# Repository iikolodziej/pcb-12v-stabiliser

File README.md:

# pcb-12v-stabiliser
pcb 12v stabiliser

# schematic

# pcb

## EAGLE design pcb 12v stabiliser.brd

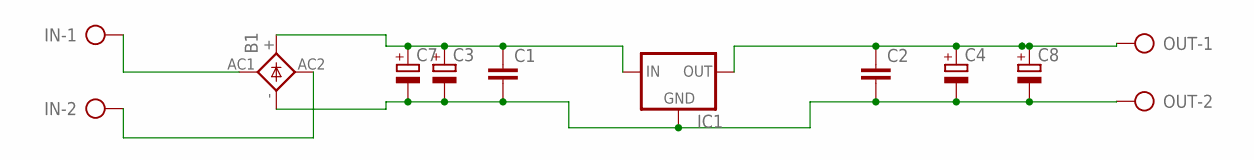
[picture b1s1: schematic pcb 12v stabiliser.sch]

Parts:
B1: 2KBB-R
C1, C2: C5/5; C5B5
C3, C4: CPOL-EUE5-8.5; E5-8,5
C7, C8: CPOL-EUE5-10.5; E5-10,5
IC1: 78XXS
IN: AK500/2-H
OUT: AK500/2-H

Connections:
GND: B1.-, C1.2, C2.2, C3.-, C4.-, C7.-, C8.-, IC1.GND, OUT.2
unnamed: B1.AC1, IN.1
unnamed: B1.AC2, IN.2
unnamed: B1.+, C1.1, C3.+, C7.+, IC1.IN
unnamed: C2.1, C4.+, C8.+, IC1.OUT, OUT.1

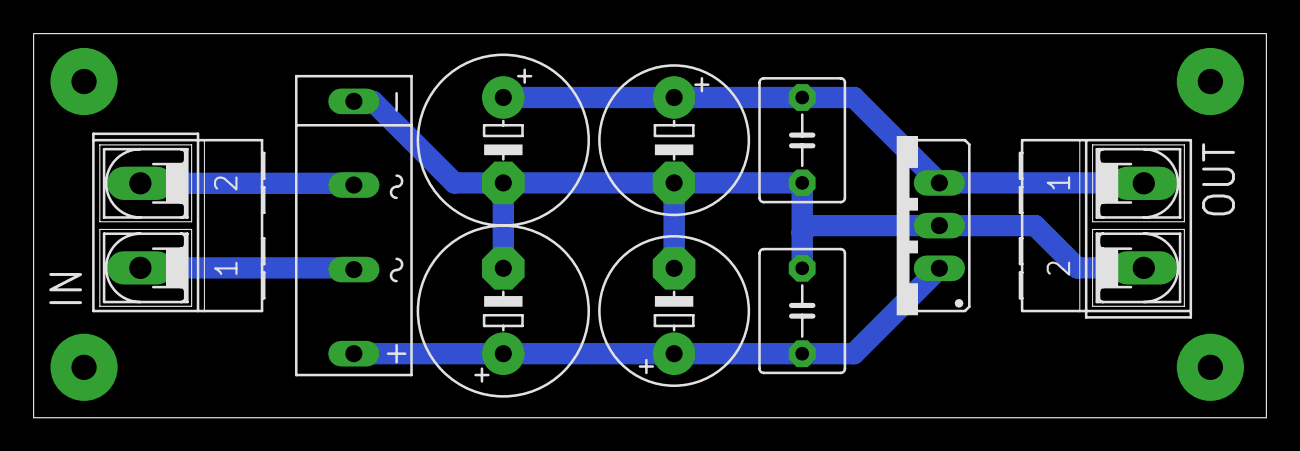
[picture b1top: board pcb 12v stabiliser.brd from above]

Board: 2 copper layers, 73.3 x 22.9 mm, 10 parts (0 on the bottom side), 5 nets.

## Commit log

2023-10-19 add design files
